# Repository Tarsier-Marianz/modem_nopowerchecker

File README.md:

# modem_nopower-currentdetector

Detect current of the device.

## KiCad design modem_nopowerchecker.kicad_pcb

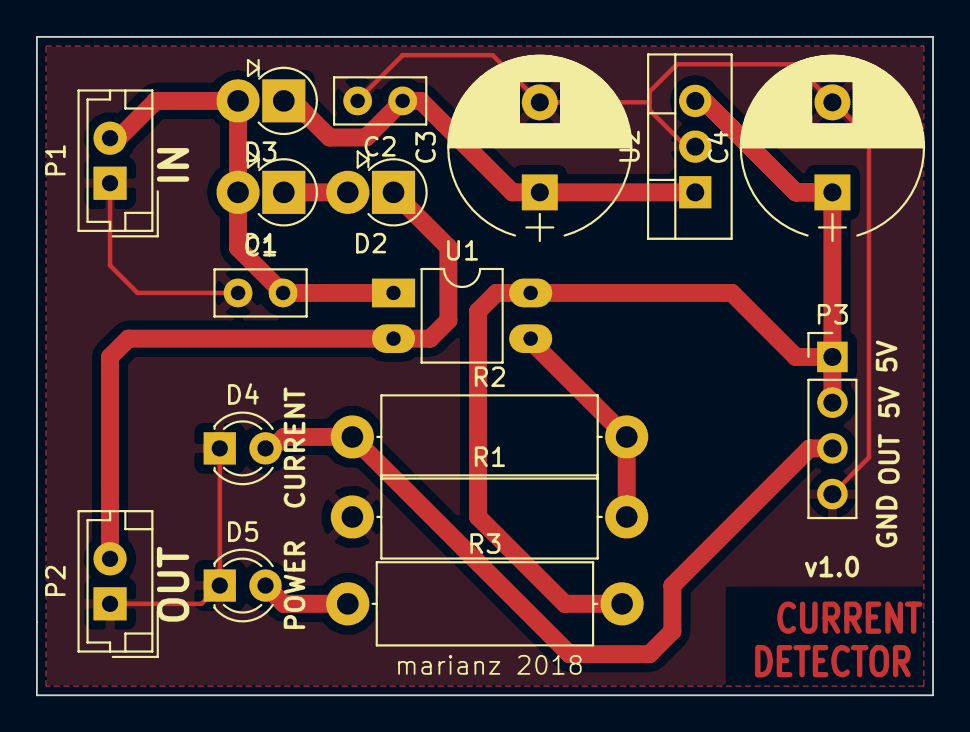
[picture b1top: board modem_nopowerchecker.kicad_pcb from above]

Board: 2 copper layers, 49.8 x 36.6 mm, 17 parts (0 on the bottom side), 9 nets.

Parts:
C1: 0.1uF; C_Disc_D5.0mm_W2.5mm_P2.50mm
C2: 0.1 uF; C_Disc_D5.0mm_W2.5mm_P2.50mm
C3, C4: 100uF/16V; CP_Radial_D10.0mm_P5.00mm
D1, D2, D3: 1N4001; D_DO-15_P2.54mm_Vertical_AnodeUp
D4, D5: LED; LED_D3.0mm
P1, P2: CONN_01X02; JST_EH_B02B-EH-A_02x2.50mm_Straight
P3: CONN_01X04; Pin_Header_Straight_1x04_Pitch2.54mm
R1, R2: 1K; R_Axial_DIN0414_L11.9mm_D4.5mm_P15.24mm_Horizontal
R3: 10K; R_Axial_DIN0414_L11.9mm_D4.5mm_P15.24mm_Horizontal
U1: PC817; DIP-4_W7.62mm_LongPads
U2: 7805; TO-220-3_Vertical

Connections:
+5V: C4.1, P3.1, P3.2, R3.2, U1.4, U2.3
GND: C1.1, C2.2, C3.2, C4.2, D4.1, D5.1, P1.1, P2.1, P3.4, R1.1, U2.2
unnamed: C1.2, D1.2, D3.2, P1.2, U1.1
unnamed: C2.1, C3.1, D3.1, U2.1
unnamed: D1.1, D2.2
unnamed: D2.1, P2.2, U1.2
unnamed: D4.2, P3.3, R2.1
unnamed: D5.2, R3.1
unnamed: R1.2, R2.2, U1.3

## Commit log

2018-10-25 +readme
2018-10-26 *change trace width
2018-10-31 +adding components value
2018-10-31 +digital output pin
2018-10-31 *traces path
2018-11-06 *converting to latest version of KiCAD
